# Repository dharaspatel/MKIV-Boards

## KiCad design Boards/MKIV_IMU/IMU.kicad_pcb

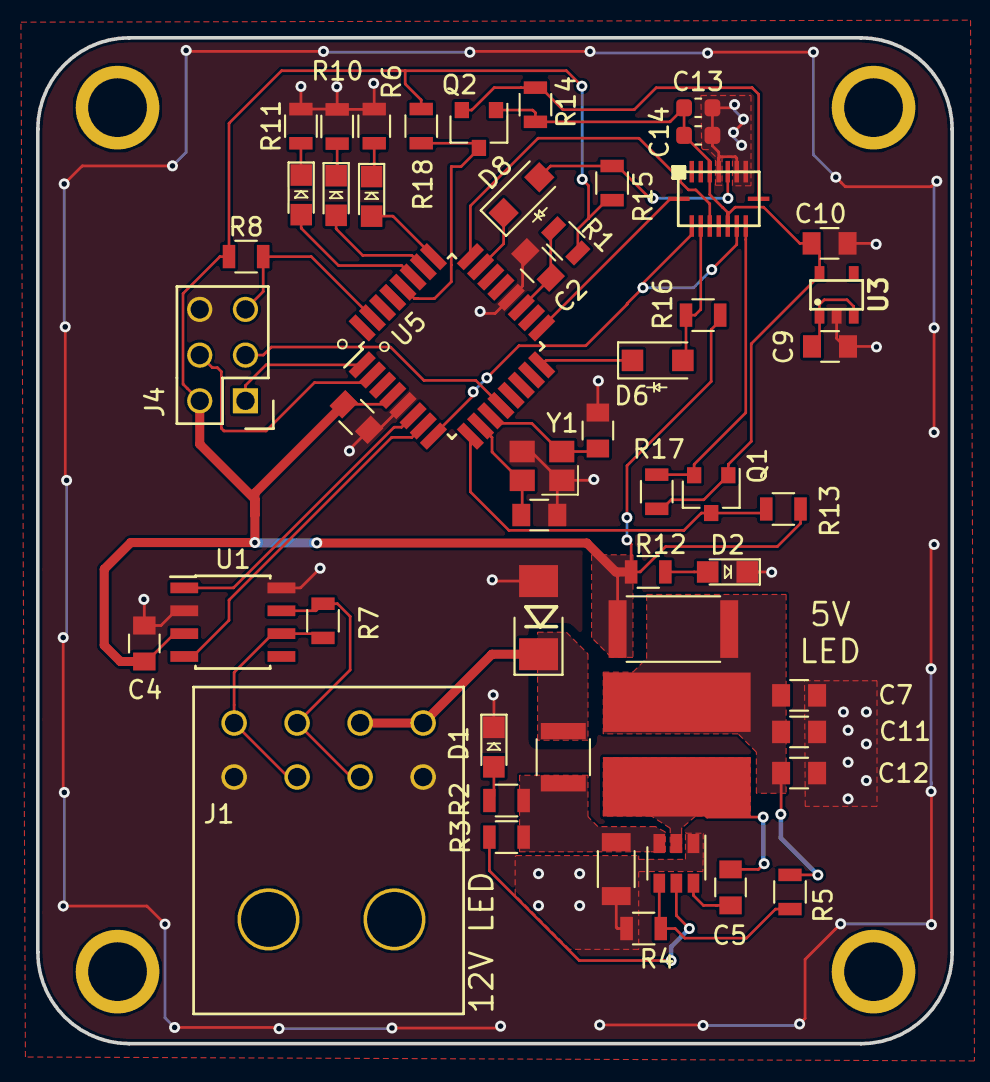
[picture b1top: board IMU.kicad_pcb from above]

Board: 2 copper layers, 50.8 x 55.9 mm, 52 parts (0 on the bottom side), 41 nets.

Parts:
C1, C4, C5, C9, C12: C_0.1uF; C_0805_OEM
C2: C_100pF; C_0805_OEM
C3: C_22uF; C_1206_OEM
C6, C8: C_30pF; C_0805_OEM
C7: C_47uF; C_0805_OEM
C10, C11: C_1uF; C_0805_OEM
C13, C14: C_100nF; C_0603_1608Metric
D1, D2, D3, D4, D5: LED_0805; LED_0805_OEM
D6, D8: SS110LW; D_SOD-123W_OEM
D7: D_Zener_18V; DO-214AA
F1: 500mA; Fuse_1210
J1: UF_8_RA; Ultrafit_8_RA
J4: CONN_02X03; Pin_Header_Straight_2x03
L1: L_4.7uH; 4.7uH_Inductor_OEM
Q1, Q2: SSM3K333R; SOT-23F
R1: R_100; R_0805_OEM
R2: R_1k; R_0805_OEM
R3, R4, R8: R_10k; R_0805_OEM
R5: R_51.1k; R_0805_OEM
R6, R10, R11, R12: R_200; R_0805_OEM
R7: R_120; R_0805_OEM
R9: R_0_Jumper; R_2512_OEM
R13, R14, R15, R16, R17, R18: R_10K; R_0805_OEM
U1: CAN_Transceiver; SOIC-8_3.9x4.9mm_Pitch1.27mm_OEM
U2: TPS561201; SOT-23-6_OEM
U3: TCR2EF33LM; SOT25
U4: BMI088; bmi088
U5: ATMEGA16M1; TQFP-32_7x7mm_Pitch0.8mm
Y1: Crystal_SMD; Crystal_SMD_FA238

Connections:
/3.3V: C10.1, C13.2, C14.1, Q1.1, Q2.1, R14.2, R17.2, U3.5, U4.3, U4.11
/12V: D7.1, F1.1, J1.3, J1.7
/12V_Fused: C3.1, F1.2, R2.1, R3.1, U2.3
/CANH: J1.2, J1.6, R7.1, U1.7
/CANL: J1.1, J1.5, R7.2, U1.6
/CS_ACCEL: D6.1, U5.16
/CS_GYRO: D8.1, U5.23
/INT1: U4.16, U5.17
/INT4: U4.13, U5.24
/MISO: J4.1, U5.1
/MISO2: U4.10, U4.15, U5.8
/MOSI: J4.4, U5.2
/MOSI2: Q1.3, R13.2, U5.9
/PLED1: D3.2, U5.25
/PLED2: D4.2, U5.26
/PLED3: D5.2, U5.27
/RESET: J4.5, R8.2, U5.31
/RXCAN: U1.4, U5.7
/SCK: J4.3, U5.12
/SCK2: Q2.3, R18.2, U5.28
/TXCAN: U1.1, U5.6
GND: C1.2, C2.2, C3.2, C4.2, C6.2, C7.2, C8.2, C9.2, C10.2, C11.2, C12.2, C13.1, C14.2, D1.1, D2.1, D7.2, J1.4, J1.8, J4.6, R4.2, R6.2, R10.2, R11.2, U1.2, U1.8, U2.1, U3.2, U4.4, U4.6, U4.7, U5.5, U5.20, Y1.2, Y1.4
unnamed: C2.1, R1.2, U5.19
unnamed: C5.1, U2.6
unnamed: C5.2, L1.1, U2.2
unnamed: C6.1, U5.11, Y1.1
unnamed: C8.1, U5.10, Y1.3
unnamed: C9.1, U3.1, U3.3
unnamed: C7.1, C11.1, C12.1, L1.2, R5.2, R9.2
unnamed: D1.2, R2.2
unnamed: D2.2, R12.2
unnamed: D3.1, R6.1
unnamed: D4.1, R10.1
unnamed: D5.1, R11.1
unnamed: D6.2, R16.1, U4.14
unnamed: D8.2, R15.2, U4.5
unnamed: Q1.2, R17.1, U4.9
unnamed: Q2.2, R14.1, U4.8
unnamed: R3.2, U2.5
unnamed: R4.1, R5.1, U2.4
VCC: C1.1, C4.1, J4.2, R1.1, R8.1, R9.1, R12.1, R13.1, R15.1, R16.2, R18.1, U1.3, U5.4

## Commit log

2019-04-15 BOM stuff
2019-04-16 schematic changes
2019-04-16 Rev 3 schematic
2019-04-16 layout rev 3
2019-04-17 IMU rev 3
2019-04-18 this is real i think
2019-04-19 rev 3 changes!
2019-04-19 Moving micromatch connectors closer to edge and reducing overall size of the board (edgecuts)
2019-04-19 Saving changes made to the board
2019-04-20 Complete rev 3 of COM board; needs review and final check off
2019-04-23 fixed fets on schematic
2019-04-23 updated fets for layout for new net list
2019-04-25 GERBER files added for rev 3
2019-04-30 Exported GERBER Files
